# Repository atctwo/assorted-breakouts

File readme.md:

# Assorted Breakout Boards
This is a collection of small breakout boards for small devices that I made with KiCad 

## Contents
- [Time Bug](#time_bug)
- [PCIe Friend](#pcie_friend)
- [Amphenol MagJack](#magjack)
- [ESP32 WROVER](#esp32-wrover)
- [I2C Microphone Breakout](#i2s_mic)
- [Alps 5 Way Switch](#5_way_switch)
- [QFN-16 breakout](#qfn16)
- [QFN-24 breakout](#qfn24)
- [QFP-80 breakout](#qfp80)
- [SOT23 Breakout](#sot23)
- [FPC (0.5mm, 30 pins)](#fpc-0.5-30)

## Time Bug (DS13xx breakout) ([`time_bug`](./time_bug/)) 

This is a breakout for the DS13xx series of RTC chips, with a MSOP-8 package (eg: DS1307, DS1308, DS1337, DS1338, DS1339, DS1341, DS1342, DS1371).  **This won't work with the DS1302 or DS1347**.  The board is designed to work with chips with the following pinout:

The two pads at the top of the board are connected to the crystal pins of the DS13xx (X1 and X2).  The board is designed such that the crystal can be placed beside the PCB, and the pins of the crystal are bent at 90°, so they can be soldered to the pads on the PCB.  The capacitor is a decoulping capacitor, and should be 0.1µF (look at the datasheet to see if there is a better capacitance for that chip).

## PCIe Friend ([`pcie_friend_2`](./pcie_friend_2/)) 

This is a very very simple debug board for PCIe x1 cards.  It basically acts as a man-in-the-middle for each of the signals on the PCIe x1 connector, hopefully making it easier to measure each signal.  

A PCIe card plugs into the device, which itself plugs into a PCIe slot.  Each pin for both connectors are brought to the middle of the board, to a 2.54mm header.  Normally most pairs of pins will be shorted using a jumper to allow the signal to pass, but debug probes can be connected to the pins to measure the signal.

Since PCIe makes use of several pairs of differential signals, using this board *might* have an impact on signal integrity, meaning there will probably be an impact on the bus' throughput.  I've tried to keep the traces length matched, but they aren't impedance matched.  I don't have the right equipment to assess how much the PCIe Friend changes the signal, so I would only recommend using it for debugging simple devices.

## Amphenol MagJack (RJMG1BD3B8K1ANR) ([`amphenol-magjack`](./amphenol-magjack/)) 

A breakout for the Amphenol RJMG1BD3B8K1ANR RJ45 connector with integrated magnetics (up to 100BASE-T).  Traces are length matched but not impedance matched, so they should only be used for testing, and not in a production version.

## ESP32 WROVER ([`esp32-wrover-breakout`](./esp32-wrover-breakout/)) 

This is a breakout board for the ESP32-WROOM-32 and ESP32-WROVER modules.  This probably won't work with the ESP32-S2.

## I²S Microphone ([`i2c-mic-breakout`](./i2c_mic_breakout/)) 

This is a breakout for the really tiny [SPH0645LM4H-B](https://cdn-shop.adafruit.com/product-files/3421/i2S+Datasheet.PDF), which is an I²S microphone.

## Alps 5 Way Switch ([`alps-5-way-switch`](./alps-5-way-switch/)) 

A breakout board for two five way switches designed by ALPS.  One of the switches is the [SKQUCAA010](https://cdn-shop.adafruit.com/datasheets/SKQUCAA010-ALPS.pdf), which is now discontinued.  The other switch is the [SKRHAxE010](https://www.mouser.co.uk/datasheet/2/15/SKRH-1370966.pdf), which isn't discontinued.

## QFN-16 ([`qfn-16-3mm-breakout`](./qfn-16-3mm-breakout/)) 

This is a breakout board for 3x3mm or 4x4mm QFN-16 chips that are 0.5mm pitch.

## QFN-24 ([`qfn-24-breakout`](./qfn-24-breakout/)) 

A breakout board for 3x3mm QFN-24 chips, with 0.4mm pitch.  It is delibrately designed so that the chip is parallel with the board so chips like IMUs point upwards when connected to a breadboard.

## QFP-80 ([`qfp-80-breakout`](./qfp-80-breakout/)) 

A breakout board for 0.4mm pitch QFP-80 ICs.

## SOT-23 ([`sot23-breakout`](./sot23-breakout/)) 

A breakout board for SOT23 chips with (up to) 6 pins.  The pins are broken out in an anticlockwise way, so pin one on the SOT23 chip correlates to pin 1 on the board.  There's a little circle beside pin one on the board.

## FPC (0.5mm, 30 pins) ([`fpc-0.5-30`](./fpc-0.5-30/)) 

A breakout board for FPC connectors of 0.5mm pitch and (up to) 30 pins.

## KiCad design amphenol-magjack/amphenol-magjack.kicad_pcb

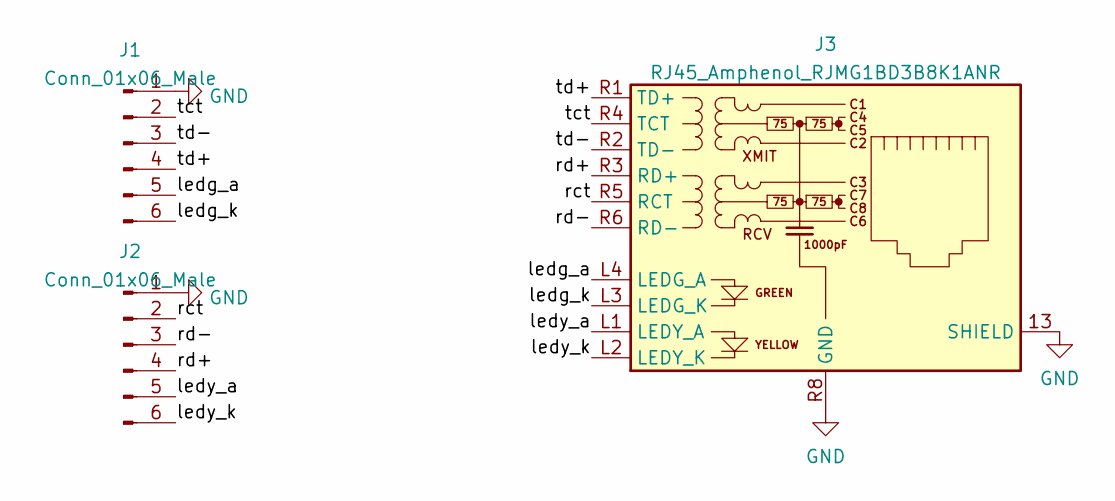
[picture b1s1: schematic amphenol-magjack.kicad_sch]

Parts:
J1, J2: Conn_01x06_Male; PinHeader_1x06_P2.54mm_Vertical
J3: RJ45_Amphenol_RJMG1BD3B8K1ANR

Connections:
/ledg_a: J1.5, J3.L4 (LEDG_A)
/ledg_k: J1.6, J3.L3 (LEDG_K)
/ledy_a: J2.5, J3.L1 (LEDY_A)
/ledy_k: J2.6, J3.L2 (LEDY_K)
/rct: J2.2, J3.R5 (RCT)
/rd+: J2.4, J3.R3 (RD+)
/rd-: J2.3, J3.R6 (RD-)
/tct: J1.2, J3.R4 (TCT)
/td+: J1.4, J3.R1 (TD+)
/td-: J1.3, J3.R2 (TD-)
GND: J1.1, J2.1, J3.13 (SHIELD), J3.R8 (GND)

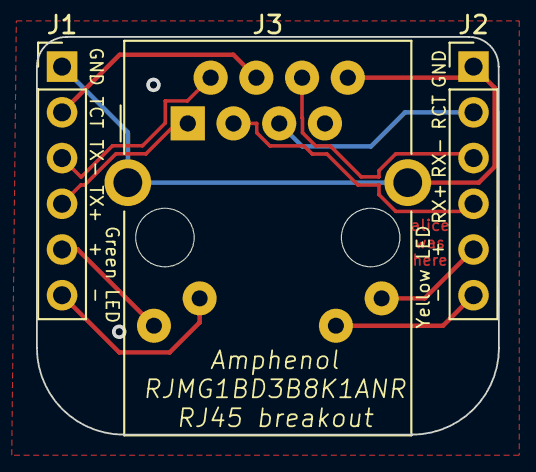
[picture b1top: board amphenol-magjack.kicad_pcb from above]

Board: 2 copper layers, 25.7 x 22.1 mm, 3 parts (0 on the bottom side), 11 nets.

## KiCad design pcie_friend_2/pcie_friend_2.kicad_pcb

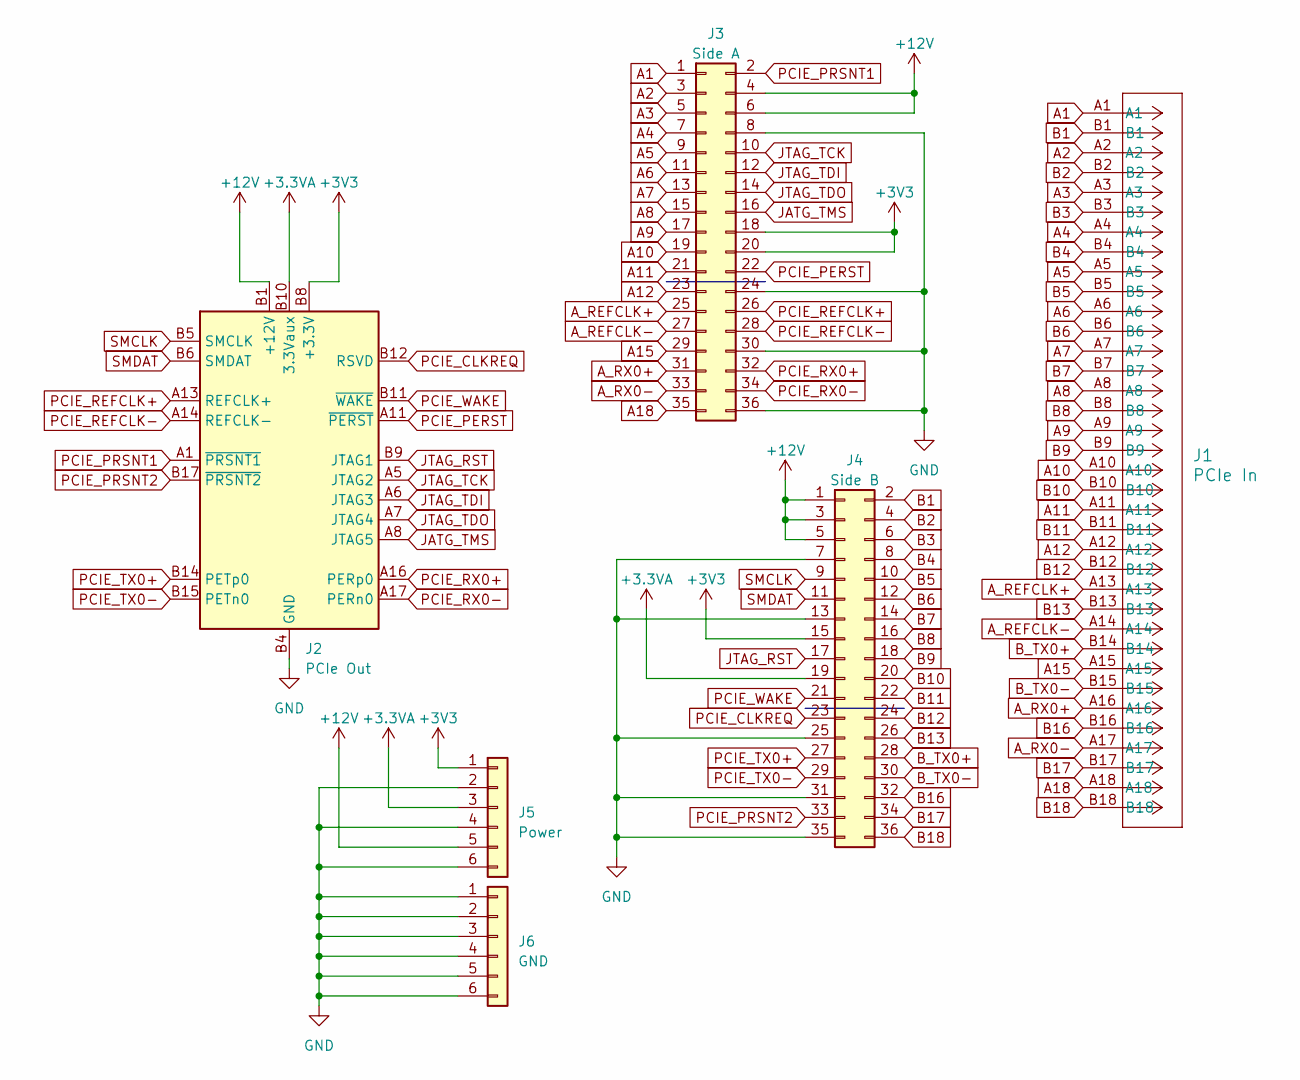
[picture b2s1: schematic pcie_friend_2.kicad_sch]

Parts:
J1: PCIe In; CONN_5-1734857-1_TEC
J2: PCIe Out; BUS_PCIexpress_x1
J3: Side A; PinHeader_2x18_P2.54mm_Vertical_SMD
J4: Side B; PinHeader_2x18_P2.54mm_Vertical_SMD
J5: Power; PinSocket_1x06_P2.54mm_Vertical
J6: GND; PinSocket_1x06_P2.54mm_Vertical

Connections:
+3.3VA: J2.B10 (3.3Vaux), J4.19, J5.3
+3V3: J2.A9 (+3.3V), J2.A10 (+3.3V), J2.B8 (+3.3V), J3.18, J3.20, J4.15, J5.1
+12V: J2.A2 (+12V), J2.A3 (+12V), J2.B1 (+12V), J2.B2 (+12V), J2.B3 (+12V), J3.4, J3.6, J4.1, J4.3, J4.5, J5.5
A1: J1.A1, J3.1
A2: J1.A2, J3.3
A3: J1.A3, J3.5
A4: J1.A4, J3.7
A5: J1.A5, J3.9
A6: J1.A6, J3.11
A7: J1.A7, J3.13
A8: J1.A8, J3.15
A9: J1.A9, J3.17
A10: J1.A10, J3.19
A11: J1.A11, J3.21
A12: J1.A12, J3.23
A15: J1.A15, J3.29
A18: J1.A18, J3.35
A_REFCLK+: J1.A13, J3.25
A_REFCLK-: J1.A14, J3.27
A_RX0+: J1.A16, J3.31
A_RX0-: J1.A17, J3.33
B1: J1.B1, J4.2
B2: J1.B2, J4.4
B3: J1.B3, J4.6
B4: J1.B4, J4.8
B5: J1.B5, J4.10
B6: J1.B6, J4.12
B7: J1.B7, J4.14
B8: J1.B8, J4.16
B9: J1.B9, J4.18
B10: J1.B10, J4.20
B11: J1.B11, J4.22
B12: J1.B12, J4.24
B13: J1.B13, J4.26
B16: J1.B16, J4.32
B17: J1.B17, J4.34
B18: J1.B18, J4.36
B_TX0+: J1.B14, J4.28
B_TX0-: J1.B15, J4.30
GND: J2.A4 (GND), J2.A12 (GND), J2.A15 (GND), J2.A18 (GND), J2.B4 (GND), J2.B7 (GND), J2.B13 (GND), J2.B16 (GND), J2.B18 (GND), J3.8, J3.24, J3.30, J3.36, J4.7, J4.13, J4.25, J4.31, J4.35, J5.2, J5.4, J5.6, J6.1, J6.2, J6.3, J6.4, J6.5, J6.6
JATG_TMS: J2.A8 (JTAG5), J3.16
JTAG_RST: J2.B9 (JTAG1), J4.17
JTAG_TCK: J2.A5 (JTAG2), J3.10
JTAG_TDI: J2.A6 (JTAG3), J3.12
JTAG_TDO: J2.A7 (JTAG4), J3.14
PCIE_CLKREQ: J2.B12 (RSVD), J4.23
PCIE_PERST: J2.A11 (~PERST), J3.22
PCIE_PRSNT1: J2.A1 (~PRSNT1), J3.2
PCIE_PRSNT2: J2.B17 (~PRSNT2), J4.33
PCIE_REFCLK+: J2.A13 (REFCLK+), J3.26
PCIE_REFCLK-: J2.A14 (REFCLK-), J3.28
PCIE_RX0+: J2.A16 (PERp0), J3.32
PCIE_RX0-: J2.A17 (PERn0), J3.34
PCIE_TX0+: J2.B14 (PETp0), J4.27
PCIE_TX0-: J2.B15 (PETn0), J4.29
PCIE_WAKE: J2.B11 (~WAKE), J4.21
SMCLK: J2.B5 (SMCLK), J4.9
SMDAT: J2.B6 (SMDAT), J4.11

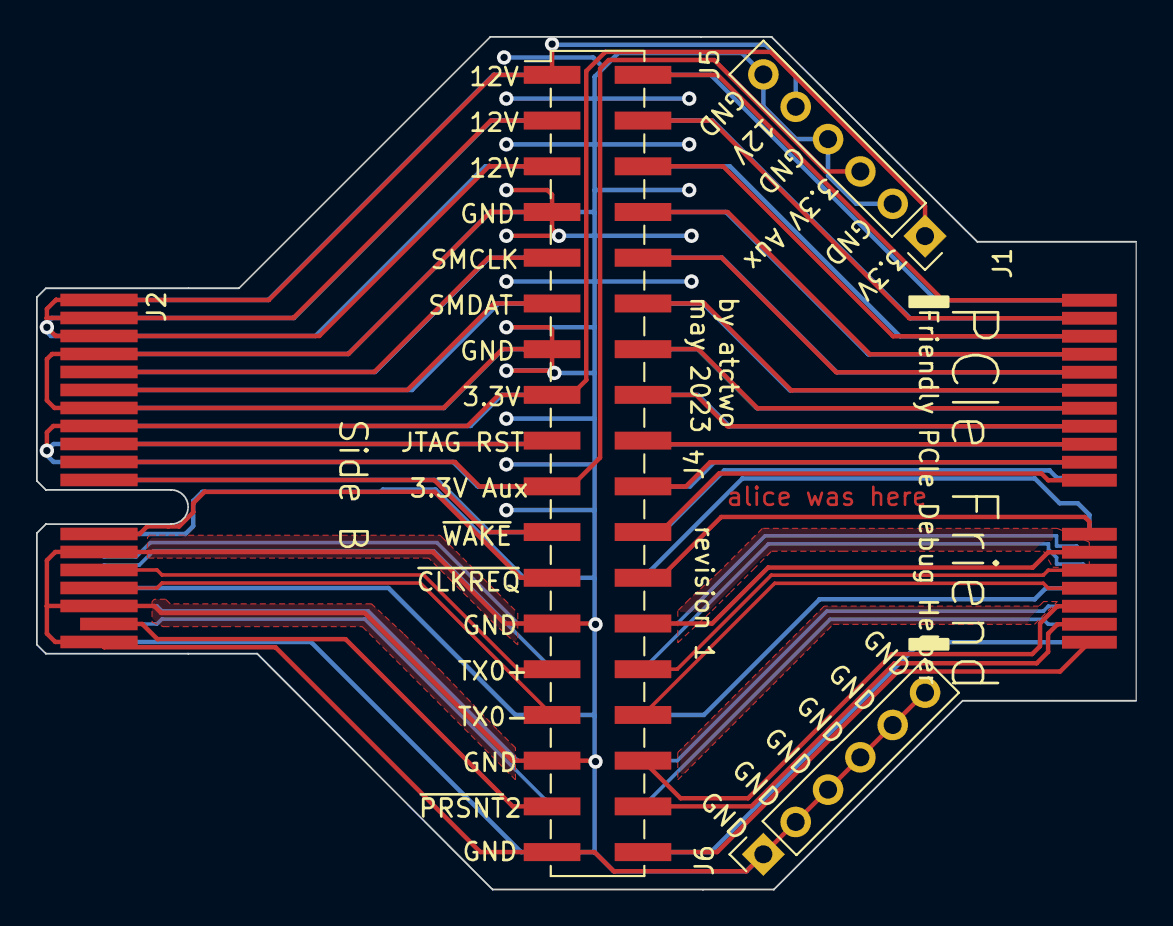
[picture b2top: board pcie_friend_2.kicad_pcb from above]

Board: 2 copper layers, 61.1 x 47.4 mm, 6 parts (1 on the bottom side), 58 nets.

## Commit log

2021-01-06 updated sot23 breakout
2021-06-27 Added Time Bug
2021-06-27 Added decoupling capacitor to readme
2024-02-19 added pcie friend
2024-02-19 added amphenol magjack
2024-02-19 added contents and links to folders
2024-02-19 added qfp-80
2024-02-19 added fpc (0.5mm, 30 pins)
